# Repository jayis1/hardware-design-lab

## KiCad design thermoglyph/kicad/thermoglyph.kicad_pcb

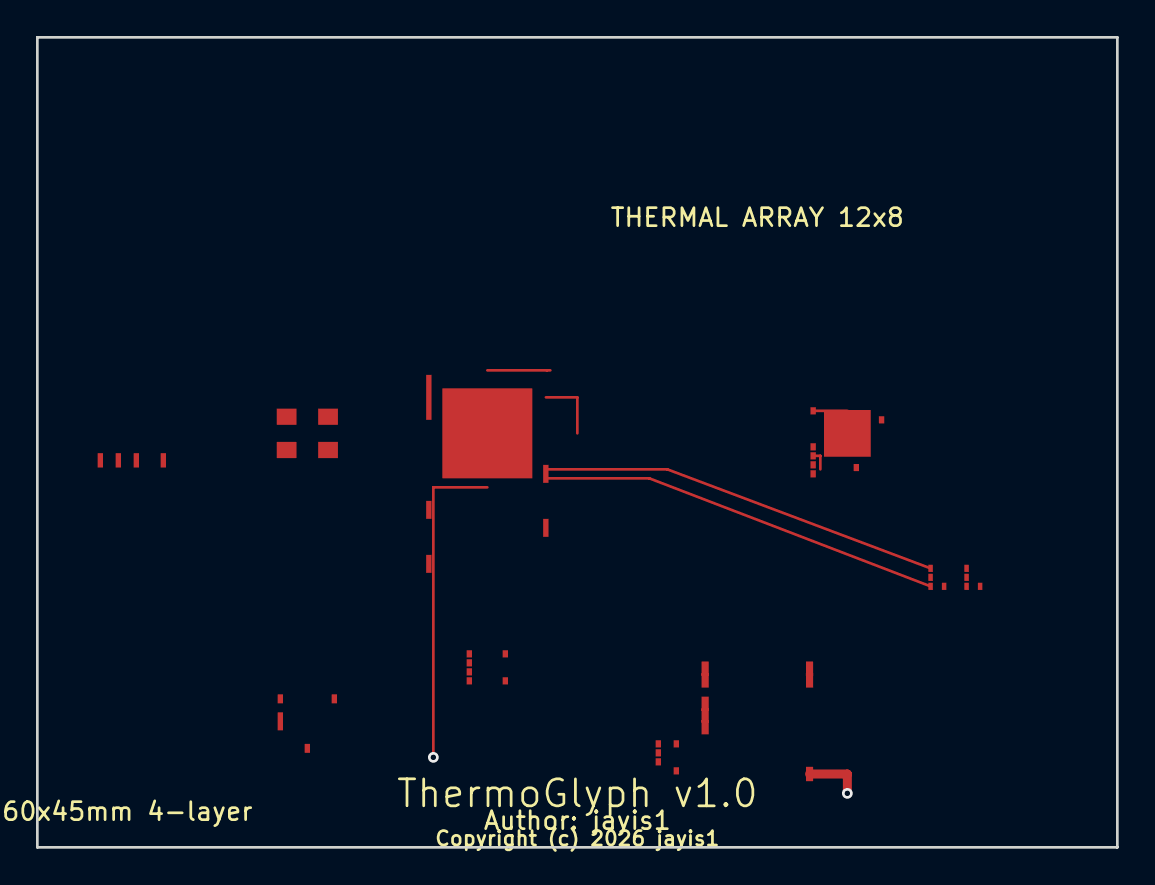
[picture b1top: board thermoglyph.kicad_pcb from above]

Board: 4 copper layers, 60.0 x 45.0 mm, 10 parts (0 on the bottom side), 9 nets.

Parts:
J1: USB-C; USB_C_Receptacle_HRO_TYPE-C-31-M-12
U1: nRF5340-QKAA-AB0-R; Nordic_AQFN-73-1EP_7x7mm_P0.5mm
U2: SX1262IMLTTR; QFN-24-1EP_4x4mm_P0.5mm_EP2.6x2.6mm
U3: TLC59711PWPR; TSSOP-20_4.4x6.5mm_P0.65mm
U8: ICM-42688-P; TDK_LCC-14_2.5x3mm_P0.5mm
U9, U10: TMP117; TI_SON-6_1.5x1.5mm_P0.5mm
U23: MAX17048; Maxim_TDFN-8_2x2mm_P0.5mm
U24: BQ25570; VQFN-14_3.5x3.5mm_P0.5mm
Y1: 32MHz; Crystal_SMD_3225-4Pin_3.2x2.5mm

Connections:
BAT+: U23.1, U24.3
GND: J1.B12, U1.47, U2.17, U2.25, U3.6, U8.9, U9.5, U10.5, U23.5, U24.8, Y1.2, Y1.4
I2C0_SCL: U1.29, U9.3, U10.3, U23.3
I2C0_SDA: U1.28, U9.2, U10.2, U23.2
USB_D+: J1.A6, U1.15
USB_D-: J1.A7, U1.16
VDD: U1.1, U2.1, U3.5, U8.8, U9.1, U10.1, U23.6, U24.6
XL1: U1.2, Y1.1
XL2: U1.3, Y1.3

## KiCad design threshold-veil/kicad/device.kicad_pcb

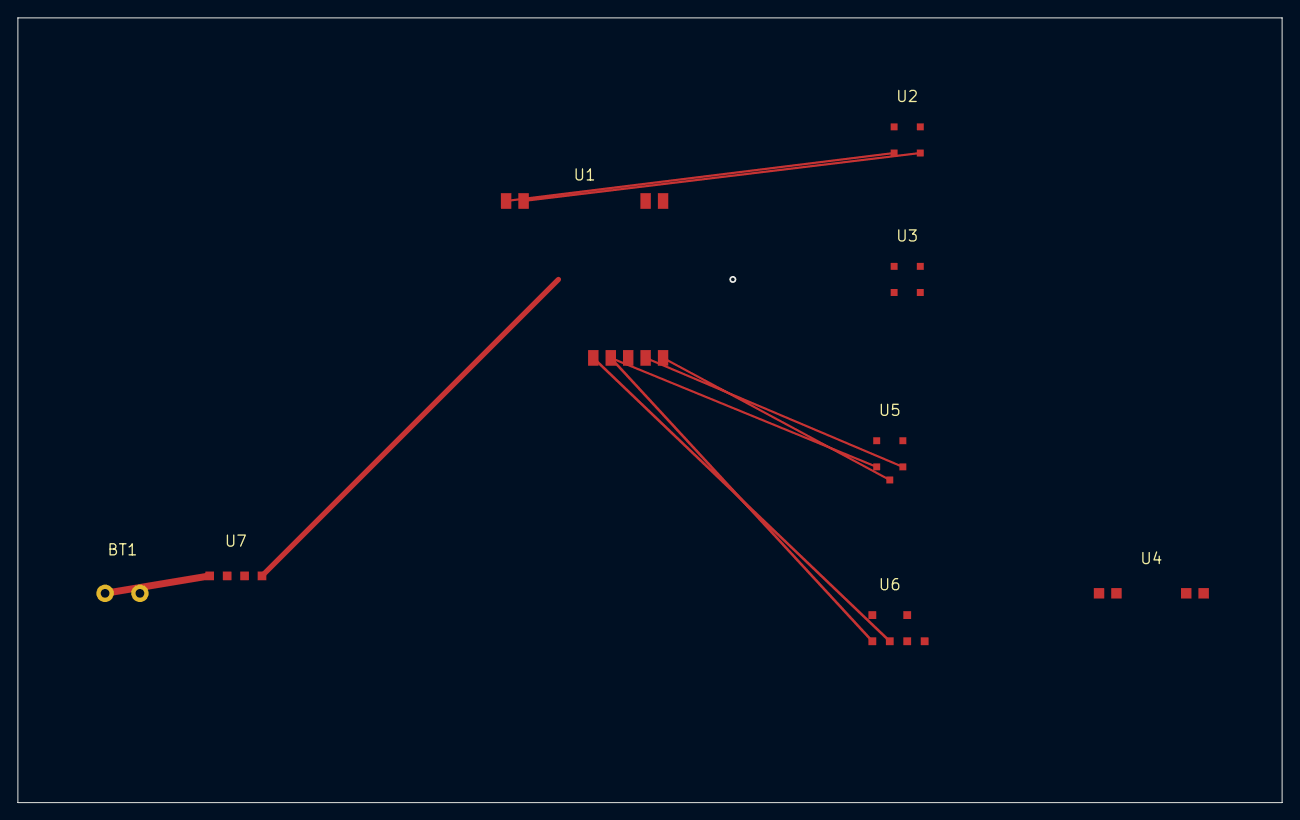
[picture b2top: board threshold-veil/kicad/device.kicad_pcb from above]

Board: 2 copper layers, 145.0 x 90.0 mm, 8 parts (0 on the bottom side), 11 nets.

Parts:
BT1: Li-Ion Pack; Battery_Pack
U1: ESP32-S3-WROOM-1
U2: BME688
U3: DPS368
U4: SEN55
U5: ICS-43434
U6: DRV8837
U7: BQ25895

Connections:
3V3: U1.1, U2.1, U3.1, U5.1
BLOWER_PWM: U1.10, U6.3
GND: BT1.2, U1.2, U2.2, U3.2, U4.2, U5.2, U6.2, U7.3
I2C_SCL: U1.5, U2.3, U3.3, U4.3
I2C_SDA: U1.6, U2.4, U3.4, U4.4
LOUVER_PWM: U1.11, U6.4
MIC_SCK: U1.8, U5.4
MIC_SD: U1.9, U5.3
MIC_WS: U1.7, U5.5
SYS_PWR: U4.1, U6.1, U7.4
VBAT: BT1.1, U7.1, U7.2

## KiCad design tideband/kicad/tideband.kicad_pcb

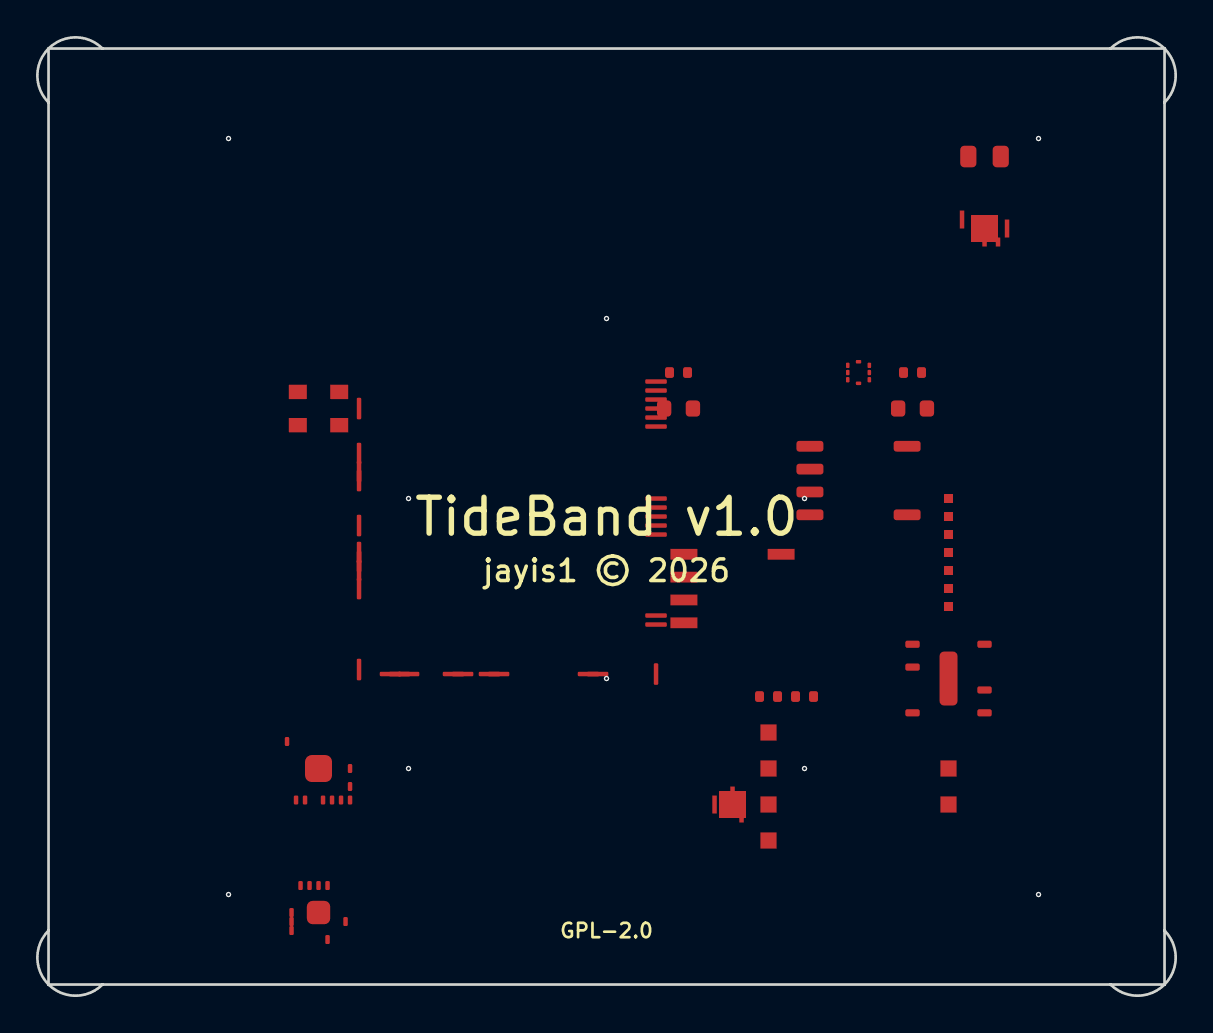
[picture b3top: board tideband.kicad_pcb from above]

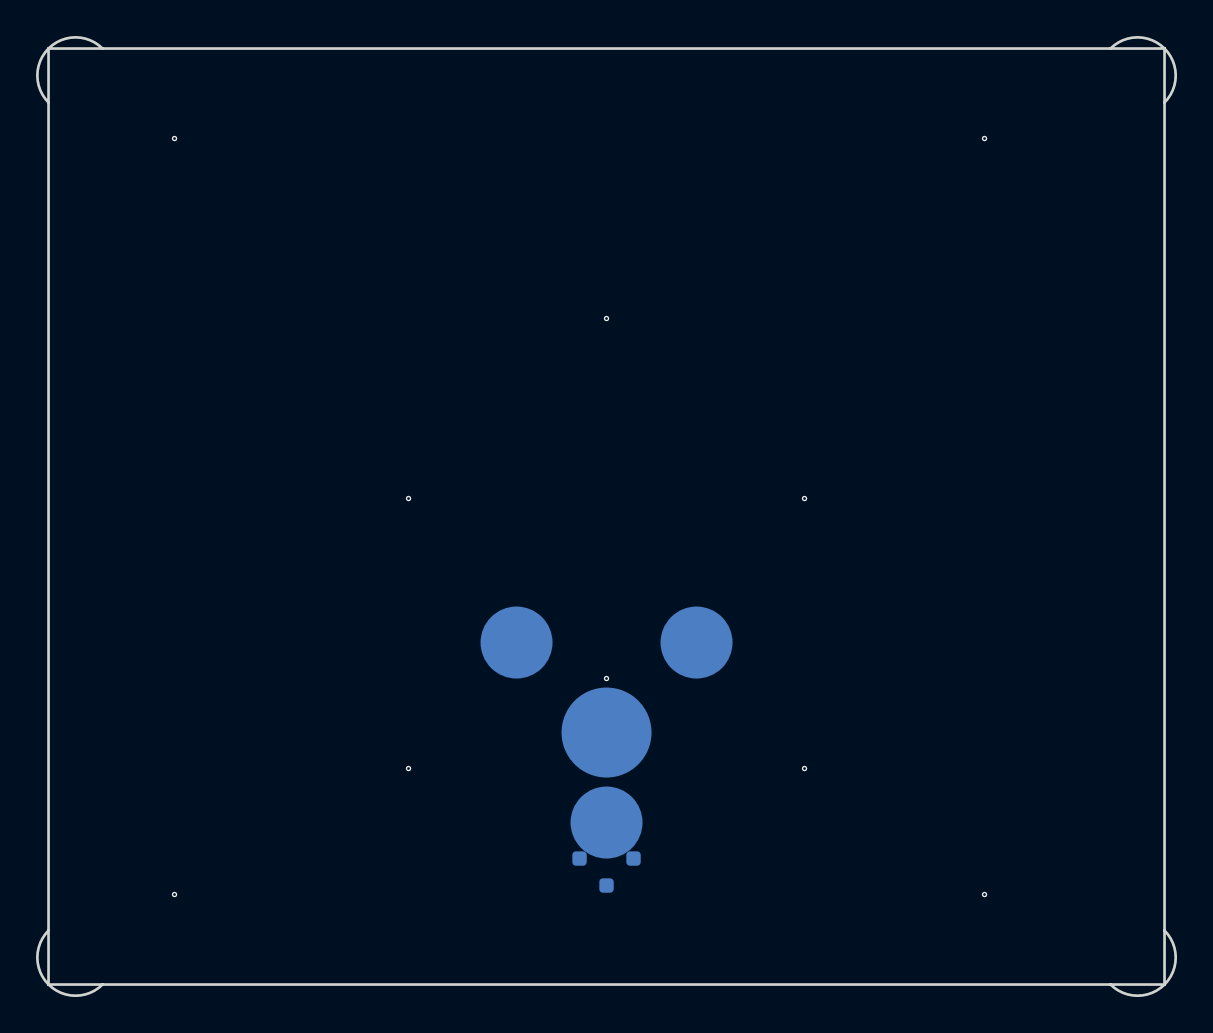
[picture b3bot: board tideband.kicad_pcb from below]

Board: 5 copper layers, 63.2 x 53.2 mm, 24 parts (5 on the bottom side), 30 nets, no tracks yet.

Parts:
C1, C3: 100nF; C_0402_1005Metric
C2, C5: 10uF; C_0603_1608Metric
L1: 2.2uH; L_0805_2012Metric
LCD1: LS013B7DH03; Sharp_LS013B7DH03
R1, R2: 4.7K; R_0402_1005Metric
RX1, RX2, RX3: PZT-5H-1MHz; PZT-5H_8mm
TX1: PZT-5H-1MHz; PZT-5H_10mm
U1: STM32H733VGT6; LQFP-100_14x14mm_P0.5mm
U2: ICM-42688-P; TFQFN-14_2x2mm_P0.4mm
U3: MMC5983MA; SOIC-8_3.9x4.9mm_P1.27mm
U4: MS5837-30BA
U5: W25N02GVZEIG; WSON-8_6x5mm_P1.27mm
U6: BMD-340-A; Ublox_BMD-340
U7: AD8333; LFCSP-24_4x4mm_P0.5mm
U8: AD9629BCPZ-20; LFCSP-20_4x4mm_P0.5mm
U9: TPS63020; VQFN-14-1EP_3x3mm_P0.5mm
U10: MAX17055; TQFN-14-1EP_3x3mm_P0.5mm
U11: PCF8523; SOIC-8_3.9x4.9mm_P1.27mm
Y1: 8MHz; Crystal_SMD_3225-4Pin_3.2x2.5mm

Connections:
3V3: C1.1, C2.1, C3.1, C5.1, L1.2, LCD1.1, R1.1, R2.1, U1.6, U1.22, U2.1, U2.9, U3.1, U3.8, U4.2, U5.8, U6.1, U7.18, U8.16, U9.9, U9.10, U9.11, U10.6, U11.4
ADC_BUSY: U1.56, U8.12
ADC_CS: U1.14, U8.7
BLE_RESET: U1.57, U6.7
BLE_RX: U1.19, U6.3
BLE_TX: U1.18, U6.4
DOPPLER_TX: TX1.1, U1.17
GND: C1.2, C2.2, C3.2, C5.2, LCD1.2, RX1.2, RX2.2, RX3.2, TX1.2, U1.50, U1.75, U2.3, U2.10, U3.2, U4.1, U5.4, U5.9, U6.2, U7.19, U7.25, U8.17, U8.21, U9.7, U9.15, U10.5, U10.15, U11.3, Y1.2, Y1.4
HSE_IN: U1.66, Y1.1
HSE_OUT: U1.67, Y1.3
I2C1_SCL: R1.2, U1.41, U4.3, U10.4, U11.6
I2C1_SDA: R2.2, U1.42, U4.4, U10.3, U11.5
I2C2_SCL: U1.45, U3.3
I2C2_SDA: U1.46, U3.4
IMU_CS: U1.78, U2.12
I_CH1: U7.9, U8.18
LCD_CS: LCD1.5, U1.66
LCD_DISP: LCD1.8, U1.67
LCD_EXTMODE: LCD1.7, U1.68
NAND_CS: U1.70, U5.1
NAND_WP: U1.71, U5.2
Q_CH1: U7.11, U8.19
SPI1_MISO: U1.35, U8.10
SPI1_MOSI: U1.36, U8.6
SPI1_SCK: U1.34, U8.5
SPI4_MISO: U1.79, U2.11, U5.6
SPI4_MOSI: LCD1.4, U1.80, U2.14, U5.5
SPI4_SCK: LCD1.3, U1.76, U2.13
VBAT: L1.1, U9.2, U9.4
VBAT_RTC: U1.1, U11.8

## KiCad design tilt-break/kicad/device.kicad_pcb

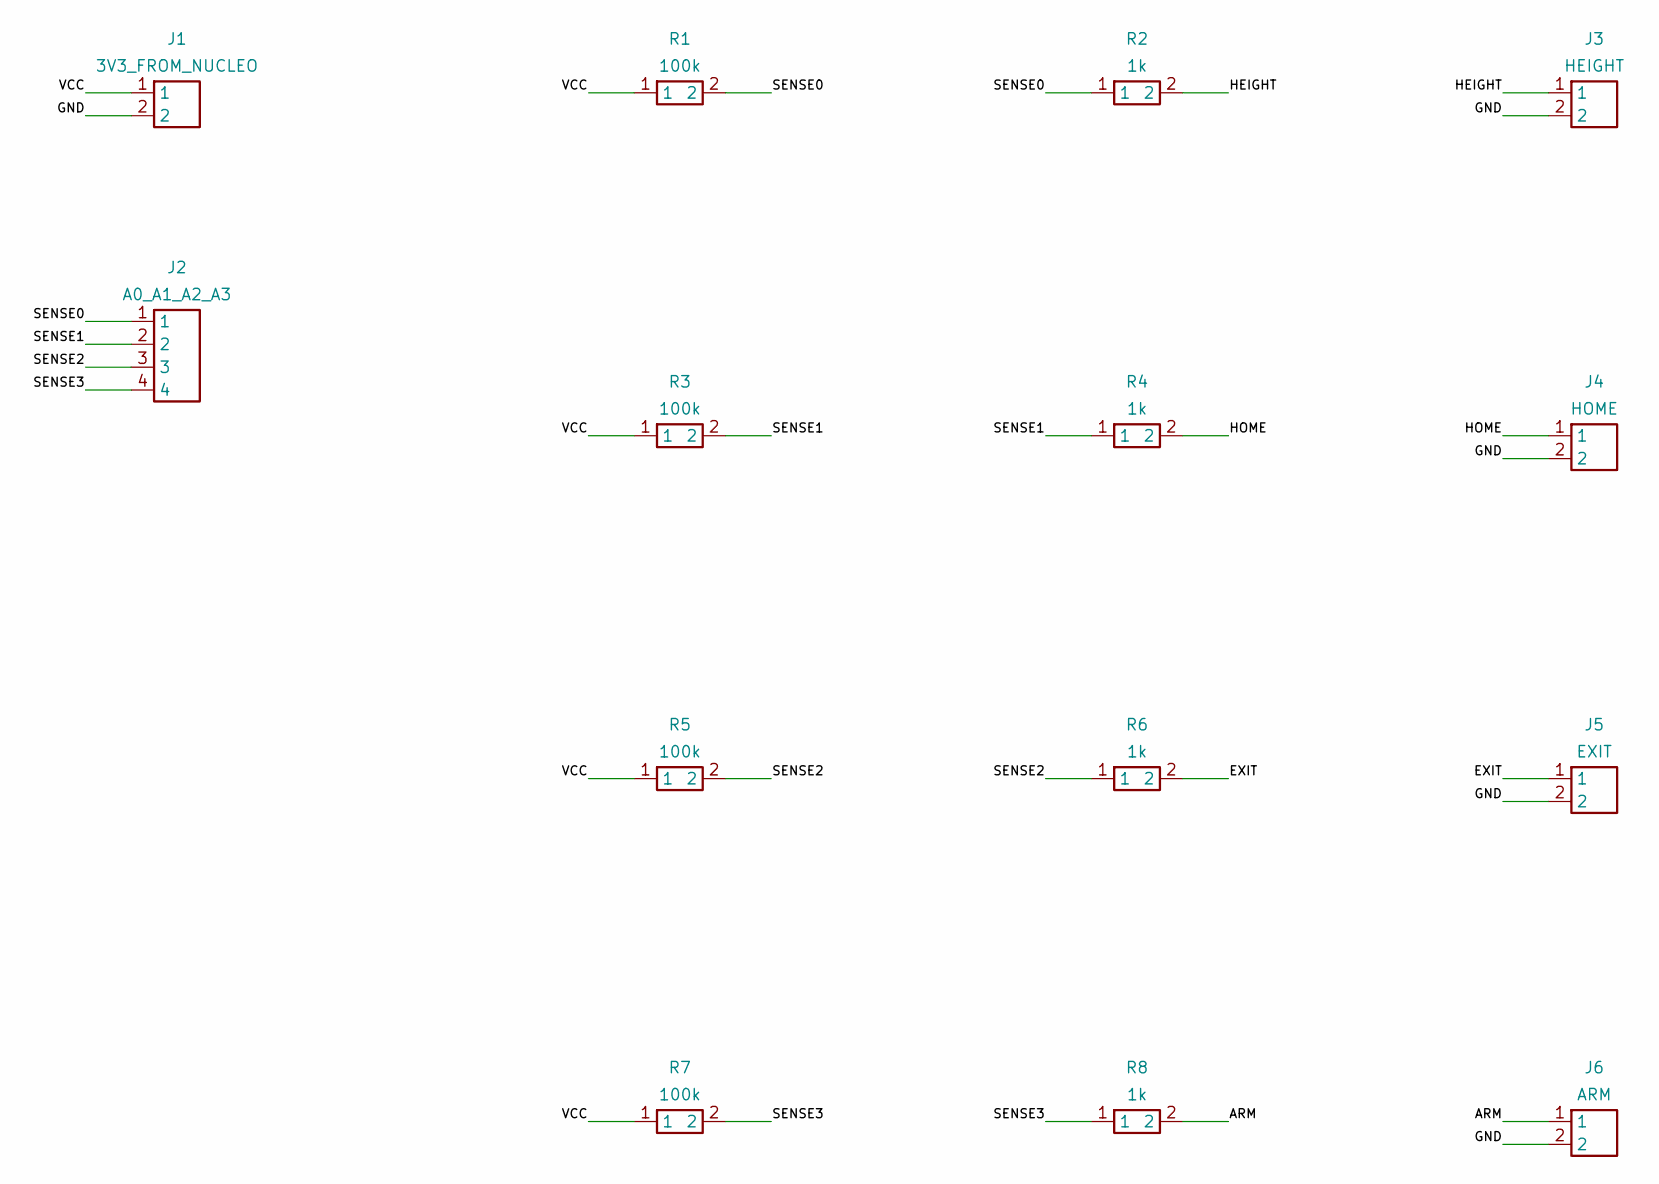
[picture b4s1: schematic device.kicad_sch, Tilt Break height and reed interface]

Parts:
J1: 3V3_FROM_NUCLEO; PinHeader_1x02_P2.54mm_Vertical
J2: A0_A1_A2_A3; PinHeader_1x04_P2.54mm_Vertical
J3: HEIGHT; PinHeader_1x02_P2.54mm_Vertical
J4: HOME; PinHeader_1x02_P2.54mm_Vertical
J5: EXIT; PinHeader_1x02_P2.54mm_Vertical
J6: ARM; PinHeader_1x02_P2.54mm_Vertical
R1, R3, R5, R7: 100k; R_Axial_DIN0207_L6.3mm_D2.5mm_P7.62mm_Horizontal
R2, R4, R6, R8: 1k; R_Axial_DIN0207_L6.3mm_D2.5mm_P7.62mm_Horizontal

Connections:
ARM: J6.1, R8.2
EXIT: J5.1, R6.2
GND: J1.2, J3.2, J4.2, J5.2, J6.2
HEIGHT: J3.1, R2.2
HOME: J4.1, R4.2
SENSE0: J2.1, R1.2, R2.1
SENSE1: J2.2, R3.2, R4.1
SENSE2: J2.3, R5.2, R6.1
SENSE3: J2.4, R7.2, R8.1
VCC: J1.1, R1.1, R3.1, R5.1, R7.1

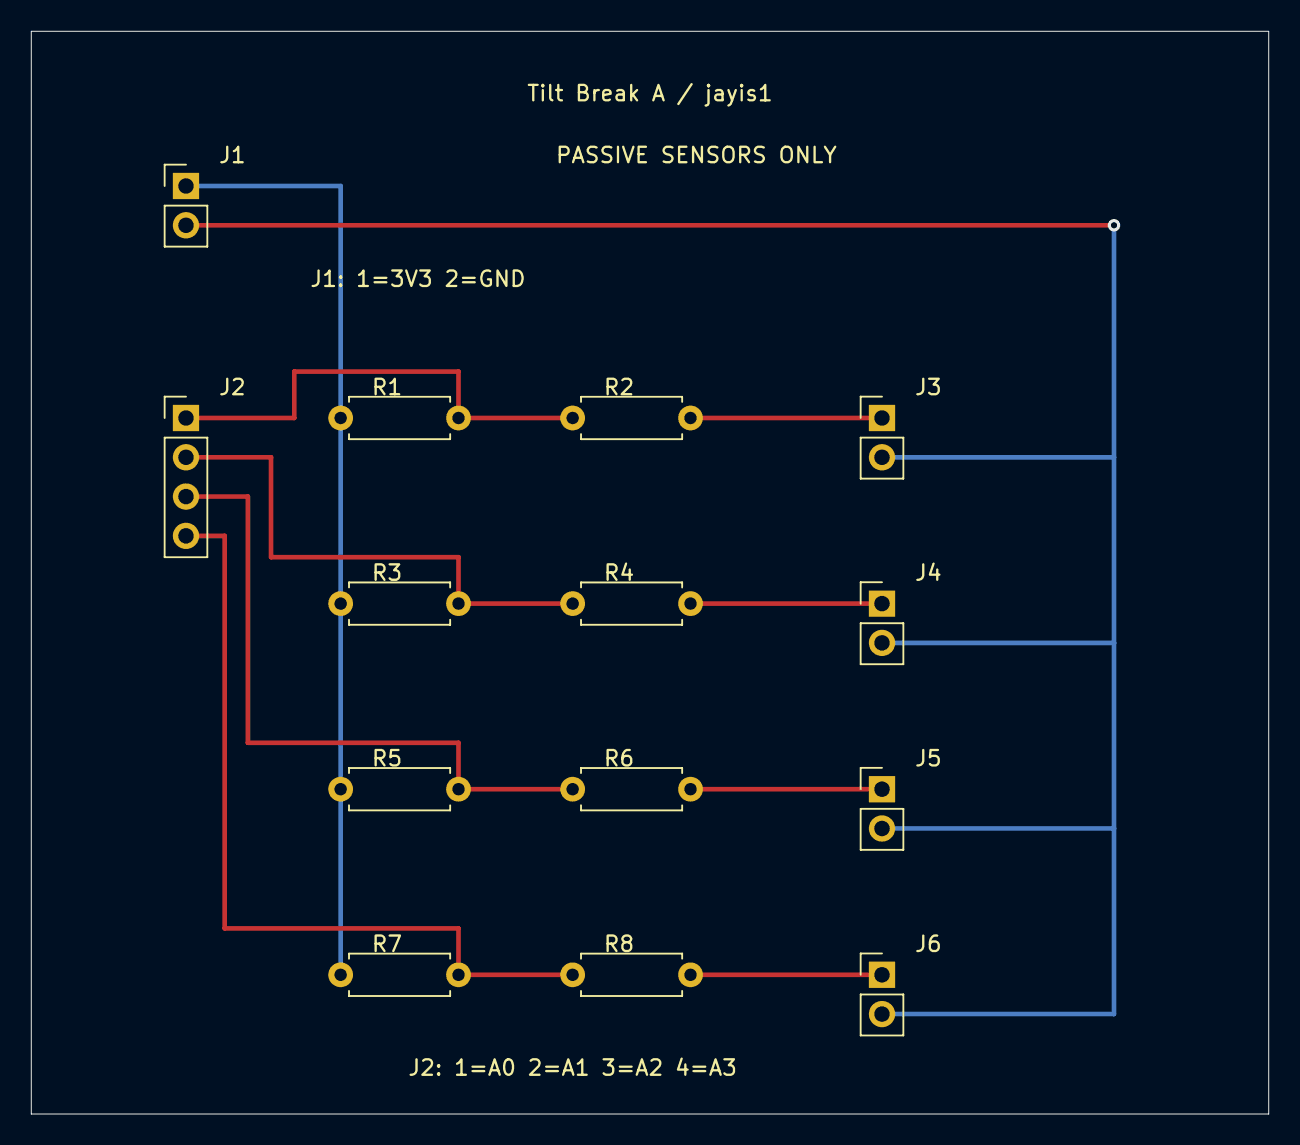
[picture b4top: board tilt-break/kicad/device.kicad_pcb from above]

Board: 2 copper layers, 80.0 x 70.0 mm, 14 parts (0 on the bottom side), 10 nets.

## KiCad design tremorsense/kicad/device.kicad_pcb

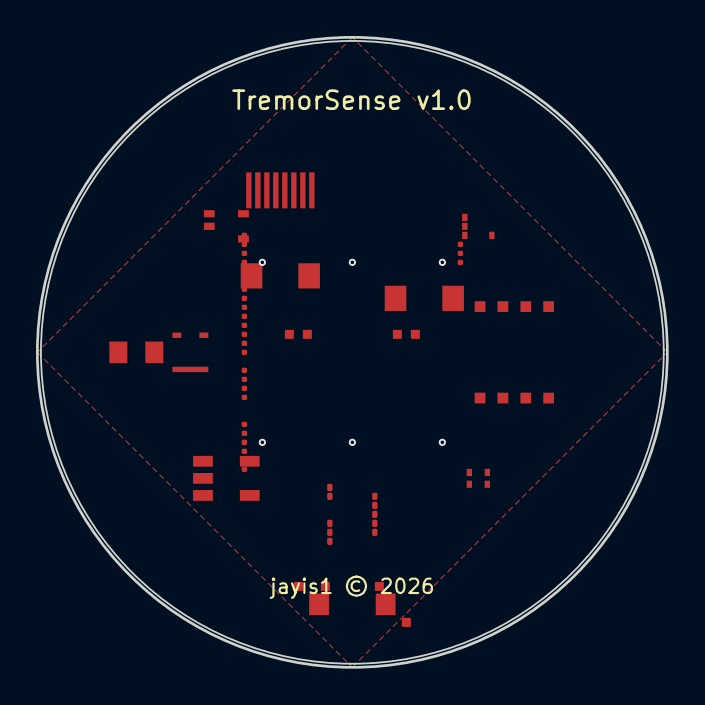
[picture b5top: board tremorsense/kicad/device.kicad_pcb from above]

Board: 4 copper layers, 35.0 x 35.0 mm, 16 parts (0 on the bottom side), 25 nets, no tracks yet.

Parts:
C1: 100nF; C_0402
C2: 4.7µF; C_0402
J1: USB-C; USB-C_16P
J2: BAT; JST-PH-2
SW1: BTN; SW_SPST_B3U-1000P
U1: nRF5340; Nordic_aQFN73
U2: ICM-42688-P; QFN-14_3x2.5mm
U3: GC9A01; FPC-24-0.5mm
U4: MX25R6435F; SOIC-8_5.3x6.2mm
U5: MAX17048; DFN-8_2x2mm
U6: MCP73831; SOT-23-5
U7: TPS62840; SOT-563
U8: SHT40; DFN-4_1.5x1.5mm
U9: LPS22HB; LGA-10_2x2.5mm
Y1: 32MHz; Crystal_SMD_3.2x2.5mm
Y2: 32.768kHz; Crystal_SMD_3215-2Pin

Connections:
BUTTON: SW1.1, U1.C1
CHARGE_STAT: U1.C8, U6.3
DISP_BL: U1.A13, U3.9
DISP_CS: U1.A7, U3.3
DISP_DC: U1.A8, U3.4
DISP_RST: U1.A12, U3.5
FLASH_CS: U1.B1, U4.1
GND: C1.2, C2.2, J1.B12, J2.2, SW1.2, U1.AA1, U2.1, U2.9, U3.2, U4.4, U5.3, U6.2, U6.4, U7.2, U8.4, U9.4
I2C_SCL: U1.C4, U5.1, U8.2, U9.2
I2C_SDA: U1.C5, U5.2, U8.3, U9.3
IMU_CS: U1.A6, U2.4
IMU_IRQ: U1.A10, U2.8
SPI0_MOSI: U1.A11, U3.7
SPI0_SCLK: U1.A9, U3.6
SPI1_MISO: U1.B4, U4.2
SPI1_MOSI: U1.B3, U4.5
SPI1_SCLK: U1.B2, U4.6
SPI2_MISO: U1.A5, U2.7
SPI2_MOSI: U1.A4, U2.6
SPI2_SCLK: U1.A3, U2.5
USB_DM: J1.A7, U1.C3
USB_DP: J1.A6, U1.C2
VBAT: J2.1, U5.4, U6.5, U7.1
VBUS: J1.A1, U6.1
VDD: C1.1, C2.1, U1.A1, U1.B12, U2.2, U2.3, U2.14, U3.1, U4.8, U5.7, U5.8, U7.3, U7.5, U8.1, U9.1

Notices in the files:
thermoglyph/kicad/thermoglyph.kicad_pcb:
Copyright (c) 2026 jayis1
License: CERN-OHL-S v2
tideband/kicad/tideband.kicad_pcb:
Copyright © 2026 jayis1. All rights reserved.
License: GPL-2.0 / CERN-OHL-W v2
jayis1 © 2026
GPL-2.0
tremorsense/kicad/device.kicad_pcb:
Copyright (c) 2026 jayis1. All rights reserved.
SPDX-License-Identifier: MIT
